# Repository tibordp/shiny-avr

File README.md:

# Shiny AVR Programmer

USB AVR ISP programmer specifically designed for ATtiny25/45/85 and ATtiny24/44/84/241/441/841 microcontroller families in DIP packages.

Blasphemeously designed with an STM32 microcontroller instead of an another AVR.

Shiny AVR programmer provides an 16 MHz clock signal, which allows programming chips that have had their fuse bits set to require an external crystal or clock signal.

# Usage

Insert the ATtiny into the DIP socket on the programmer. Please make sure it is oriented the right way. It should also work for programming the ATtinys in circuit (unless there is circuitry wired to it that would interfere, which is likely, since ATtinys don't have dedicated programming pins), but since there is no standard ISP header on the board, you will need to provide an adapter cable.

Shiny AVR powers ATtinys with 3.3V.

## Arduino

Shiny AVR Programmer will present to the host computer as a virtual USB serial port. It can be used seamlessly from Arduino IDE by
selecting **Tools > Programmer > Arduino as ISP** and selecting the appropriate serial port.

## avrdude

Use `-c arduino` command-line parameter.

## PlatformIO

It requires some modifications to use the [avrdude.conf from ATTinyCore](https://github.com/SpenceKonde/ATTinyCore/blob/master/avr/avrdude.conf) instead of the default one bundled with PlatformIO (`chip_erase_delay` is too low in the stock one).

Example config for ATtiny85

```ini
[env:attiny85]
platform = atmelavr
board = attiny85
upload_protocol = custom
upload_flags =
    -C$PROJECT_PACKAGES_DIR/framework-arduino-avr-attiny/avrdude.conf
    -p$BOARD_MCU
    -P$UPLOAD_PORT
    -b$UPLOAD_SPEED
    -carduino
upload_command = avrdude $UPLOAD_FLAGS -U flash:w:$SOURCE:i

upload_port = <your serial port device here>
upload_speed = 19200
board_build.f_cpu = 16000000L
board_fuses.lfuse = 0xD1
board_fuses.hfuse = 0xDF
board_fuses.efuse = 0xFF
```

Example config for ATtiny84

```ini
[env:attiny84]
platform = atmelavr
board = attiny84
upload_protocol = custom
upload_flags =
    -C$PROJECT_PACKAGES_DIR/framework-arduino-avr-attiny/avrdude.conf
    -p$BOARD_MCU
    -P$UPLOAD_PORT
    -b$UPLOAD_SPEED
    -carduino
upload_command = avrdude $UPLOAD_FLAGS -U flash:w:$SOURCE:i

upload_port = <your serial port device here>
upload_speed = 19200
board_build.f_cpu = 8000000L
board_fuses.lfuse = 0x62
board_fuses.hfuse = 0xDF
board_fuses.efuse = 0xFF
```

# Hardware

The schematic and PCB layout are in the [kicad](./kicad) folder.

# Firmware

Firmware is based on [ArduinoISP](https://github.com/arduino/arduino-examples/blob/main/examples/11.ArduinoISP/ArduinoISP/ArduinoISP.ino) with the 
appropriate modifications for the specifics of hardware (LEDs, SPI parameters, ...) and it adds the capability to provide external clock to be able
to program ATtinys that have had their fuses set to rely on external clock or crystal.

# Roadmap

- High voltage programming support for chips `RSTDISBL` or debugWIRE fuse bits set  
- Managed power supply or a PTC to prevent damaging the chips 
  that are inserted upside down in the socket.

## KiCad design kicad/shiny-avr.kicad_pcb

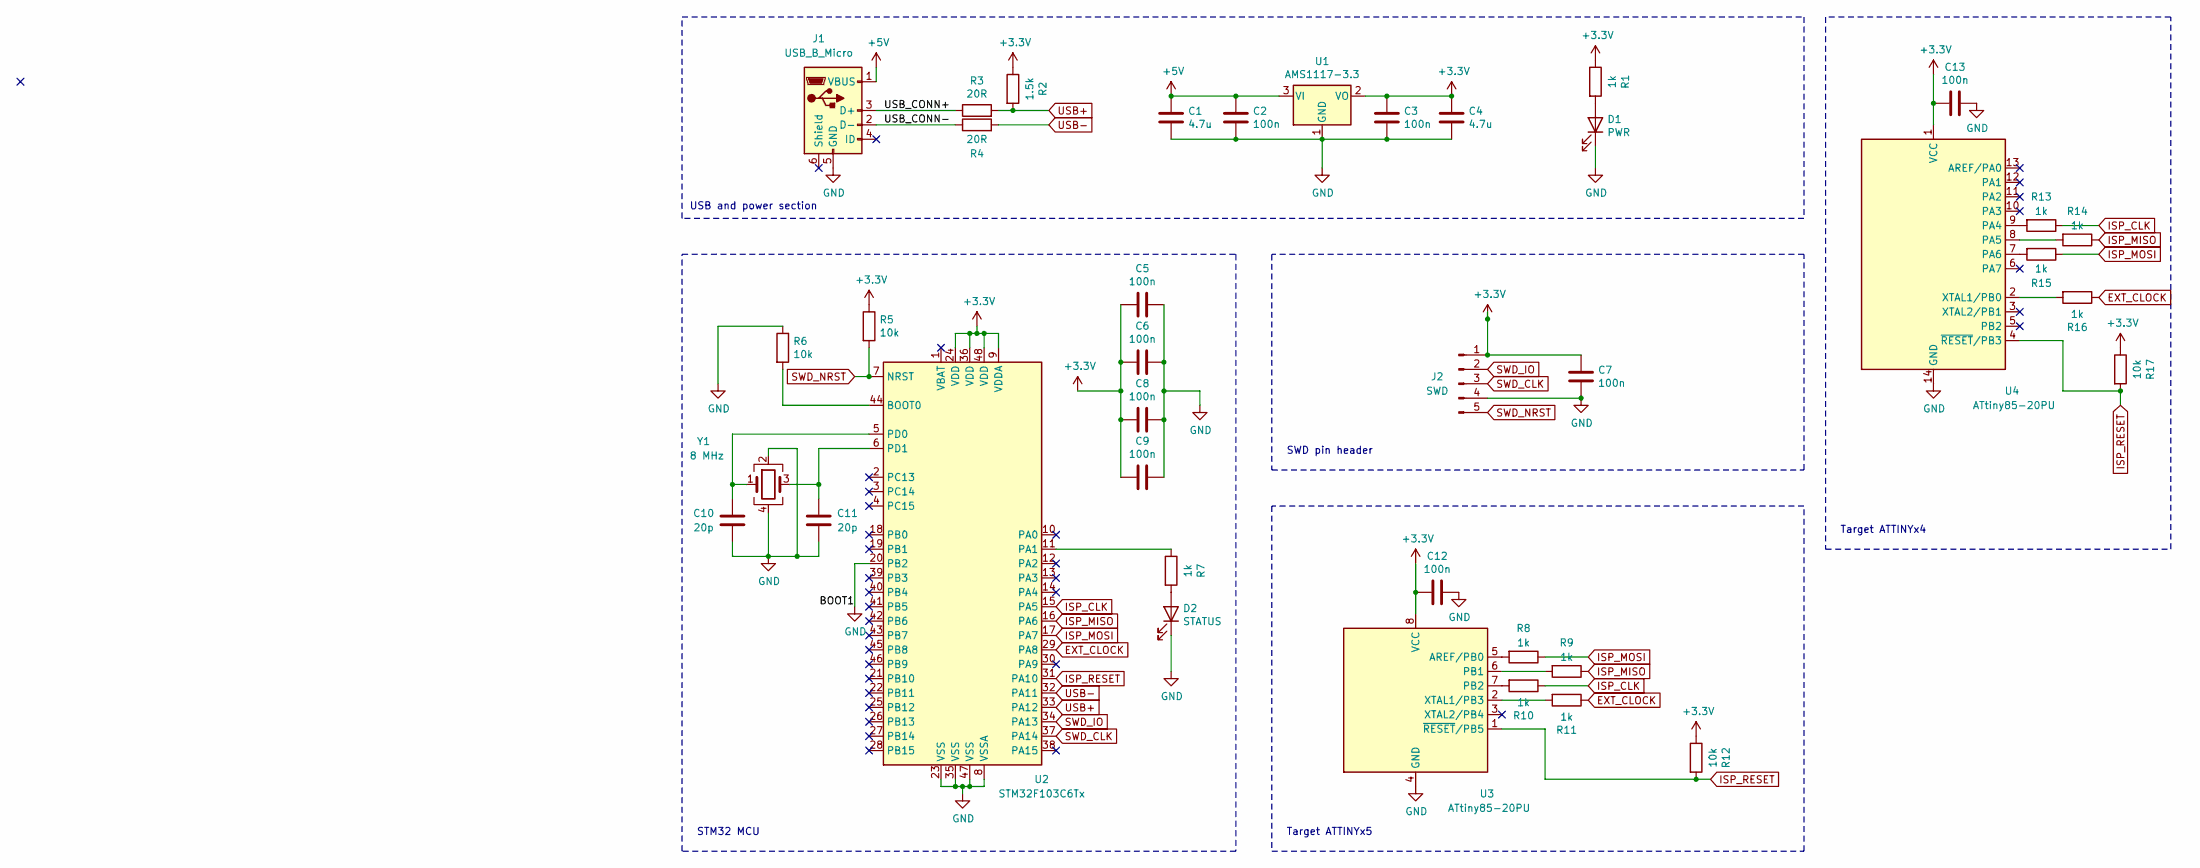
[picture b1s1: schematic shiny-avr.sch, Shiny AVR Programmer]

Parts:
C1, C4: 4.7u; C_0805_2012Metric_Pad1.18x1.45mm_HandSolder
C2, C3, C5, C6, C7, C8, C9, C12, C13: 100n; C_0805_2012Metric_Pad1.18x1.45mm_HandSolder
C10, C11: 20p; C_0805_2012Metric_Pad1.18x1.45mm_HandSolder
D1: PWR; LED_0805_2012Metric_Pad1.15x1.40mm_HandSolder
D2: STATUS; LED_0805_2012Metric_Pad1.15x1.40mm_HandSolder
J1: USB_B_Micro; 101181930001LF
J2: SWD; PinHeader_1x05_P2.54mm_Vertical
R1, R7, R8, R9, R10, R11, R13, R14, R15, R16: 1k; R_0805_2012Metric_Pad1.20x1.40mm_HandSolder
R2: 1.5k; R_0805_2012Metric_Pad1.20x1.40mm_HandSolder
R3, R4: 20R; R_0805_2012Metric_Pad1.20x1.40mm_HandSolder
R5, R6, R12, R17: 10k; R_0805_2012Metric_Pad1.20x1.40mm_HandSolder
U1: AMS1117-3.3; SOT-223-3_TabPin2
U2: STM32F103C6Tx; LQFP-48_7x7mm_P0.5mm
U3: ATtiny85-20PU; DIP-8_W7.62mm
U4: ATtiny85-20PU; DIP-14_W7.62mm
Y1: 8 MHz; Crystal_SMD_5032-4Pin_5.0x3.2mm

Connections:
+3V3: C3.1, C4.1, C5.2, C6.2, C7.1, C8.2, C9.2, C12.2, C13.2, J2.1, R1.1, R2.1, R5.1, R12.1, R17.1, U1.2 (VO), U2.9 (VDDA), U2.24 (VDD), U2.36 (VDD), U2.48 (VDD), U3.8 (VCC), U4.1 (VCC)
+5V: C1.1, C2.1, J1.1 (VBUS), U1.3 (VI)
/USB_CONN+: J1.3 (D+), R3.1
/USB_CONN-: J1.2 (D-), R4.1
EXT_CLOCK: R11.1, R16.1, U2.29 (PA8)
GND: C1.2, C2.2, C3.2, C4.2, C5.1, C6.1, C7.2, C8.1, C9.1, C10.2, C11.2, C12.1, C13.1, D1.1 (K), D2.1 (K), J1.5 (GND), J2.4, R6.1, U1.1 (GND), U2.8 (VSSA), U2.20 (PB2), U2.23 (VSS), U2.35 (VSS), U2.47 (VSS), U3.4 (GND), U4.14 (GND), Y1.2, Y1.4
ISP_CLK: R10.1, R13.1, U2.15 (PA5)
ISP_MISO: R9.1, R14.1, U2.16 (PA6)
ISP_MOSI: R8.1, R15.1, U2.17 (PA7)
ISP_RESET: R12.2, R17.2, U2.31 (PA10), U3.1 (~RESET~/PB5), U4.4 (~RESET~/PB3)
unnamed: C10.1, U2.5 (PD0), Y1.1
unnamed: C11.1, U2.6 (PD1), Y1.3
unnamed: D1.2 (A), R1.2
unnamed: D2.2 (A), R7.2
unnamed: R6.2, U2.44 (BOOT0)
unnamed: R7.1, U2.11 (PA1)
unnamed: R8.2, U3.5 (AREF/PB0)
unnamed: R9.2, U3.6 (PB1)
unnamed: R10.2, U3.7 (PB2)
unnamed: R11.2, U3.2 (XTAL1/PB3)
unnamed: R13.2, U4.9 (PA4)
unnamed: R14.2, U4.8 (PA5)
unnamed: R15.2, U4.7 (PA6)
unnamed: R16.2, U4.2 (XTAL1/PB0)
SWD_CLK: J2.3, U2.37 (PA14)
SWD_IO: J2.2, U2.34 (PA13)
SWD_NRST: J2.5, R5.2, U2.7 (NRST)
USB+: R2.2, R3.2, U2.33 (PA12)
USB-: R4.2, U2.32 (PA11)

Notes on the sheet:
USB and power section
STM32 MCU
Target ATTINYx5
SWD pin header
Target ATTINYx4

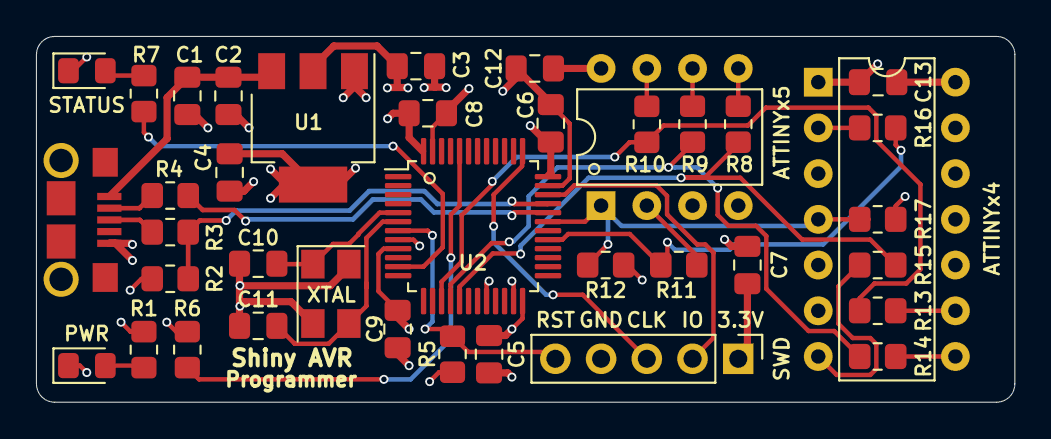
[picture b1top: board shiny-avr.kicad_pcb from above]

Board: 4 copper layers, 54.4 x 20.3 mm, 39 parts (0 on the bottom side), 29 nets.

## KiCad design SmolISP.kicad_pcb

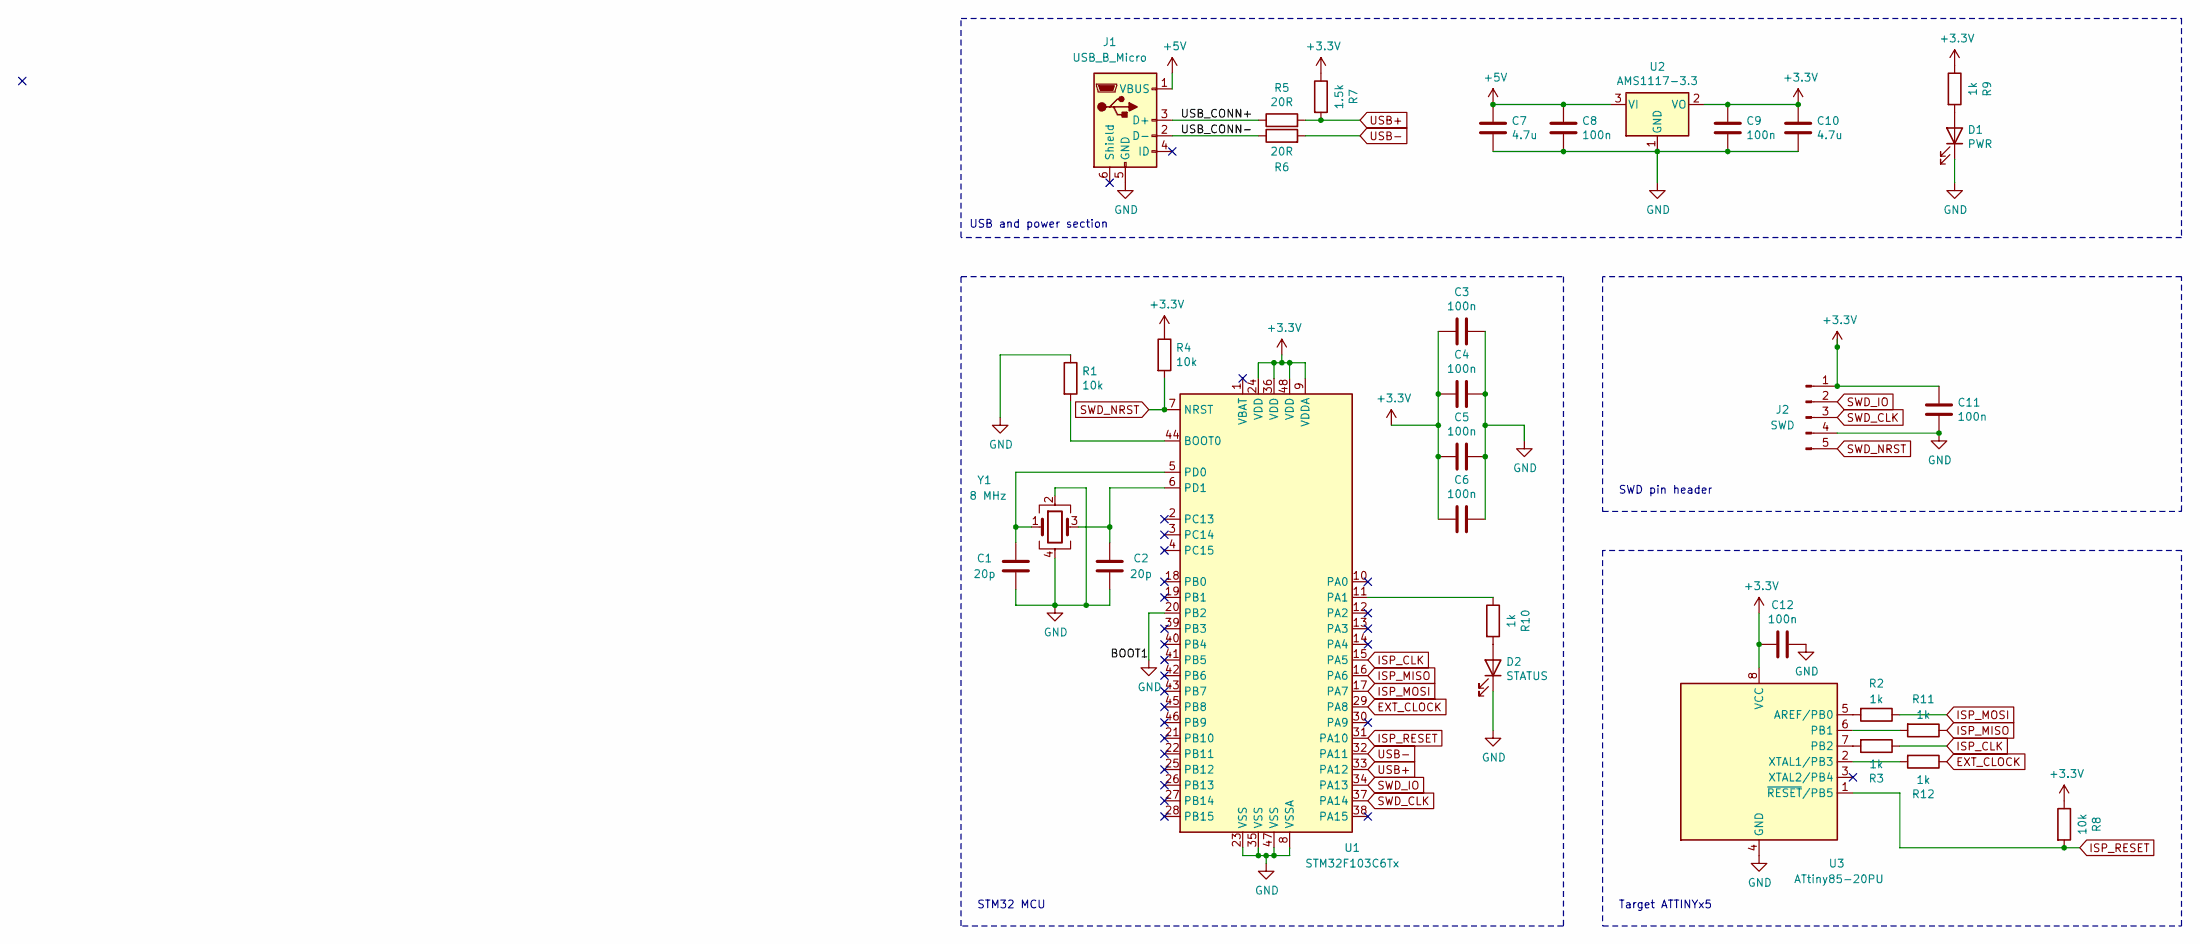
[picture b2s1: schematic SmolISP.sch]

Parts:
C1, C2: 20p; C_0805_2012Metric_Pad1.18x1.45mm_HandSolder
C3, C4, C5, C6, C8, C9, C11, C12: 100n; C_0805_2012Metric_Pad1.18x1.45mm_HandSolder
C7, C10: 4.7u; C_0805_2012Metric_Pad1.18x1.45mm_HandSolder
D1: PWR; LED_0805_2012Metric_Pad1.15x1.40mm_HandSolder
D2: STATUS; LED_0805_2012Metric_Pad1.15x1.40mm_HandSolder
J1: USB_B_Micro; 101181930001LF
J2: SWD; PinHeader_1x05_P2.54mm_Vertical
R1, R4, R8: 10k; R_0805_2012Metric_Pad1.20x1.40mm_HandSolder
R2, R3, R9, R10, R11, R12: 1k; R_0805_2012Metric_Pad1.20x1.40mm_HandSolder
R5, R6: 20R; R_0805_2012Metric_Pad1.20x1.40mm_HandSolder
R7: 1.5k; R_0805_2012Metric_Pad1.20x1.40mm_HandSolder
U1: STM32F103C6Tx; LQFP-48_7x7mm_P0.5mm
U2: AMS1117-3.3; SOT-223-3_TabPin2
U3: ATtiny85-20PU; DIP-8_W7.62mm
Y1: 8 MHz; Crystal_SMD_5032-4Pin_5.0x3.2mm

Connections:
+3V3: C3.2, C4.2, C5.2, C6.2, C9.1, C10.1, C11.1, C12.2, J2.1, R4.1, R7.1, R8.1, R9.1, U1.9 (VDDA), U1.24 (VDD), U1.36 (VDD), U1.48 (VDD), U2.2 (VO), U3.8 (VCC)
+5V: C7.1, C8.1, J1.1 (VBUS), U2.3 (VI)
/USB_CONN+: J1.3 (D+), R5.1
/USB_CONN-: J1.2 (D-), R6.1
EXT_CLOCK: R12.1, U1.29 (PA8)
GND: C1.2, C2.2, C3.1, C4.1, C5.1, C6.1, C7.2, C8.2, C9.2, C10.2, C11.2, C12.1, D1.1 (K), D2.1 (K), J1.5 (GND), J2.4, R1.1, U1.8 (VSSA), U1.20 (PB2), U1.23 (VSS), U1.35 (VSS), U1.47 (VSS), U2.1 (GND), U3.4 (GND), Y1.2, Y1.4
ISP_CLK: R3.1, U1.15 (PA5)
ISP_MISO: R11.1, U1.16 (PA6)
ISP_MOSI: R2.1, U1.17 (PA7)
ISP_RESET: R8.2, U1.31 (PA10), U3.1 (~RESET~/PB5)
unnamed: C1.1, U1.5 (PD0), Y1.1
unnamed: C2.1, U1.6 (PD1), Y1.3
unnamed: D1.2 (A), R9.2
unnamed: D2.2 (A), R10.2
unnamed: R1.2, U1.44 (BOOT0)
unnamed: R2.2, U3.5 (AREF/PB0)
unnamed: R3.2, U3.7 (PB2)
unnamed: R10.1, U1.11 (PA1)
unnamed: R11.2, U3.6 (PB1)
unnamed: R12.2, U3.2 (XTAL1/PB3)
SWD_CLK: J2.3, U1.37 (PA14)
SWD_IO: J2.2, U1.34 (PA13)
SWD_NRST: J2.5, R4.2, U1.7 (NRST)
USB+: R5.2, R7.2, U1.33 (PA12)
USB-: R6.2, U1.32 (PA11)

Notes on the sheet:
USB and power section
STM32 MCU
Target ATTINYx5
SWD pin header

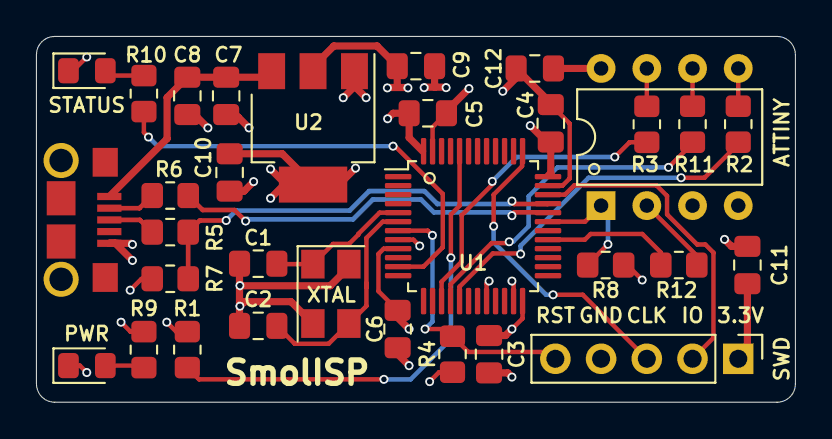
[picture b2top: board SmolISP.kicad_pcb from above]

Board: 4 copper layers, 42.2 x 20.3 mm, 32 parts (0 on the bottom side), 25 nets.

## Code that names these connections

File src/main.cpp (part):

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#define SPI_CLOCK (1000000 / 6)

// Configure which pins to use:
#define RESET PA10
#define LED_STATUS PA1

#define PIN_MOSI PA7
#define PIN_MISO PA6
#define PIN_SCK PA5
#define PIN_EXT_CLOCK PA8

#define BAUDRATE 19200

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  reset_target(true);

  // Start the external clock at 16 MHz for ATtinys that require external clock or crystal
  pinMode(PIN_EXT_CLOCK, OUTPUT);
  analogWriteResolution(2);
  analogWriteFrequency(16000000);
  analogWrite(PIN_EXT_CLOCK, 1);
  pinMode(RESET, OUTPUT);
  
  SPI.begin();
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  // We're about to take the target out of reset so configure SPI pins as input
  pinMode(PIN_MOSI, INPUT);
  pinMode(PIN_SCK, INPUT);
  pinMode(PIN_EXT_CLOCK, INPUT);

  reset_target(false);
  pinMode(RESET, INPUT);
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
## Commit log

2021-01-12 Initial commit.
2021-01-12 Changes after PCB review
2021-01-12 Update screenshots
2021-01-12 Stash
2021-01-13 Relicense + rename
2021-01-13 ci: Add CI
2021-01-13 Fix DRC
2021-01-13 ci: Add CI (#1)
    * ci: Add CI
    * fix
    * fix
    * fix
    * Fix DRC
2021-01-20 feat: Add support for ATtinyx4
2021-01-20 Add support for ATtiny24/44/48 (#2)
    * feat: Add support for ATtinyx4
    * fix
2021-02-03 Add firmware
2021-02-03 fixup: cosmetic changes
2021-02-03 ci: Add CI (#1)
2021-02-03 Add support for ATtiny24/44/48 (#2)
2021-02-03 fix: Swapped pins 6 and 7 on ATtinyX4 socket
2021-02-03 fix: images
2021-02-03 fix: Swapped pins 6 and 7 on ATtinyX4 socket (#4)
    * fix: Swapped pins 6 and 7 on ATtinyX4 socket
    * fix: images
2021-02-06 feat: Add external clock support
2021-02-06 feat: Add external clock support (#5)
2021-04-11 docs: Update docs to use -carduino for AVRdude
    stk500v1 only works on Mac, it seems.
2021-04-11 docs: Update docs

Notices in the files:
src/main.cpp:
Based on ArduinoISP, original copyright (c) 2008-2011 Randall Bohn
